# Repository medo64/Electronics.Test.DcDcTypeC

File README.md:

DC-DC Test Board
================

Mini test board providing 5V output from 20V TypeC.

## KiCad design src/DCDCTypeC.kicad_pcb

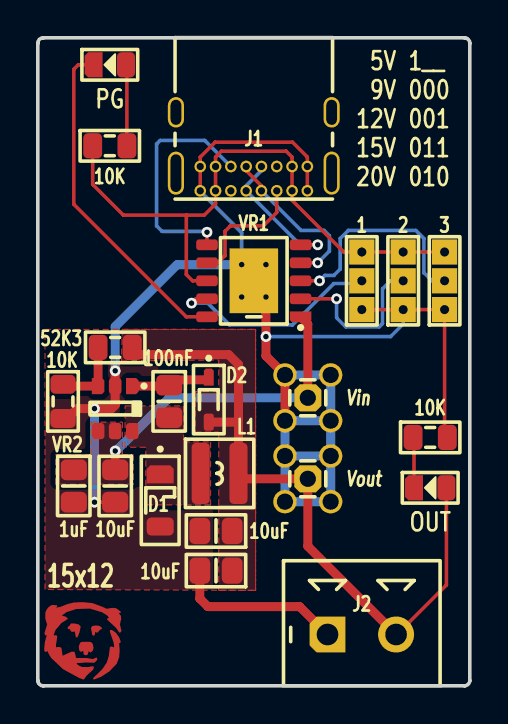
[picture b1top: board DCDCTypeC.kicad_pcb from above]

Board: 2 copper layers, 24.0 x 36.0 mm, 24 parts (0 on the bottom side), 17 nets.

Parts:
C1: 100nF; C (0805)
C2: 1uF; C (0805)
C3, C4, C5: 10uF; C (0805)
D1: B260S1F; D Shottky (SOD123F)
D2: CUS08F30; D (SOD323)
DS1: PG; DS (0805)
DS2: OUT; DS (0805)
ICON: Medo64; ICON Medo64
J1: ‎USB4085; J USB C 2.0 Receptacle (16w)
J2: MCV 1,5/2; J Phoenix MCV (2w)
JP1: 1; JP Dual Test (1205)
JP2: 2; JP Dual Test (1205)
JP3: 3; JP Dual Test (1205)
L1: 22uH; L Inductor (3.0x3.0)
R1, R2, R3: 10K; R (0805)
R4: 52K3; R (0805)
TP1: Vin; TP MMCX (3.5mm)
TP2: Vout; TP MMCX (3.5mm)
VR1: CH224K; VR PD [CH224K] (ESSOP-10')
VR2: MCP16301; VR Buck Adjustable 600mA [MCP16301] (SOT23-6)

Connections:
BOOST: C1.1, D2.1, VR2.1
FB: R3.1, R4.2, VR2.3
GND: C2.2, C3.2, C4.2, C5.2, D1.2, J1.A01, J1.A12, J1.B01, J1.B12, J2.1, JP1.1, JP2.1, JP3.1, R2.2, R3.2, TP1.2, TP2.2, VR1.11, VR2.2
LED_OUT: DS2.1, R2.1
LED_PG: DS1.2, R1.2
PG: DS1.1, VR1.10
SW: C1.2, D1.1, L1.1, VR2.6
USB_CC1: J1.A05, VR1.7
USB_CC2: J1.B05, VR1.6
USB_CFG1: JP1.2, VR1.9
USB_CFG2: JP2.2, VR1.2
USB_CFG3: JP3.2, VR1.3
USB_DM: J1.A07, J1.B07, VR1.5
USB_DP: J1.A06, J1.B06, VR1.4
Vin: C2.1, C3.1, TP1.1, VR1.1, VR2.4, VR2.5
Vout: C4.1, C5.1, D2.2, DS2.2, J2.2, L1.2, R4.1, TP2.1
Vusb: J1.A04, J1.A09, J1.B04, J1.B11, JP1.3, JP2.3, JP3.3, R1.1, VR1.8

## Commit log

2025-03-04 Added test points
